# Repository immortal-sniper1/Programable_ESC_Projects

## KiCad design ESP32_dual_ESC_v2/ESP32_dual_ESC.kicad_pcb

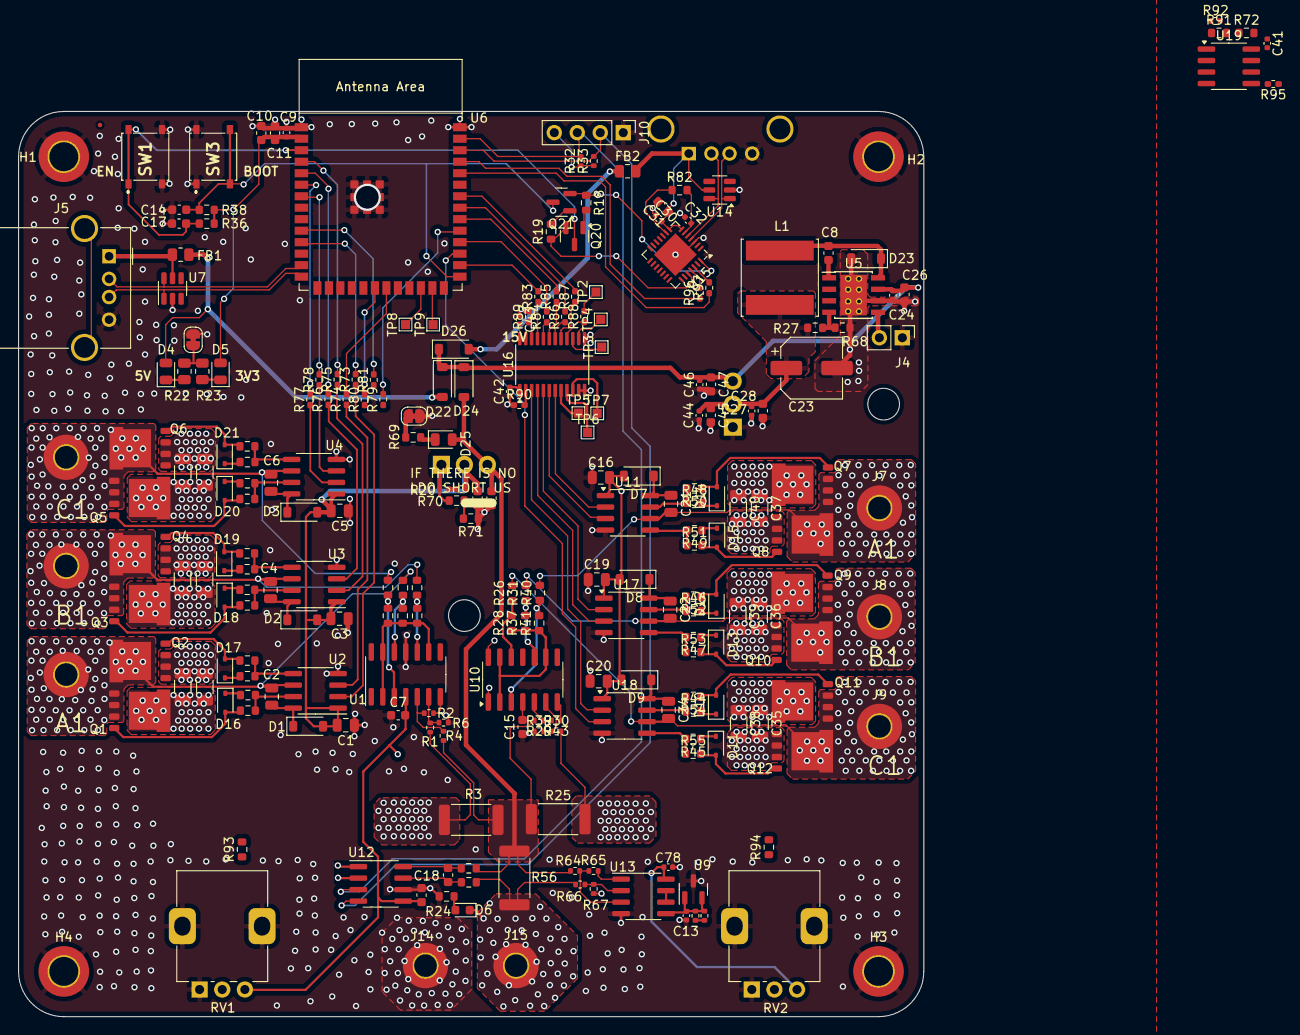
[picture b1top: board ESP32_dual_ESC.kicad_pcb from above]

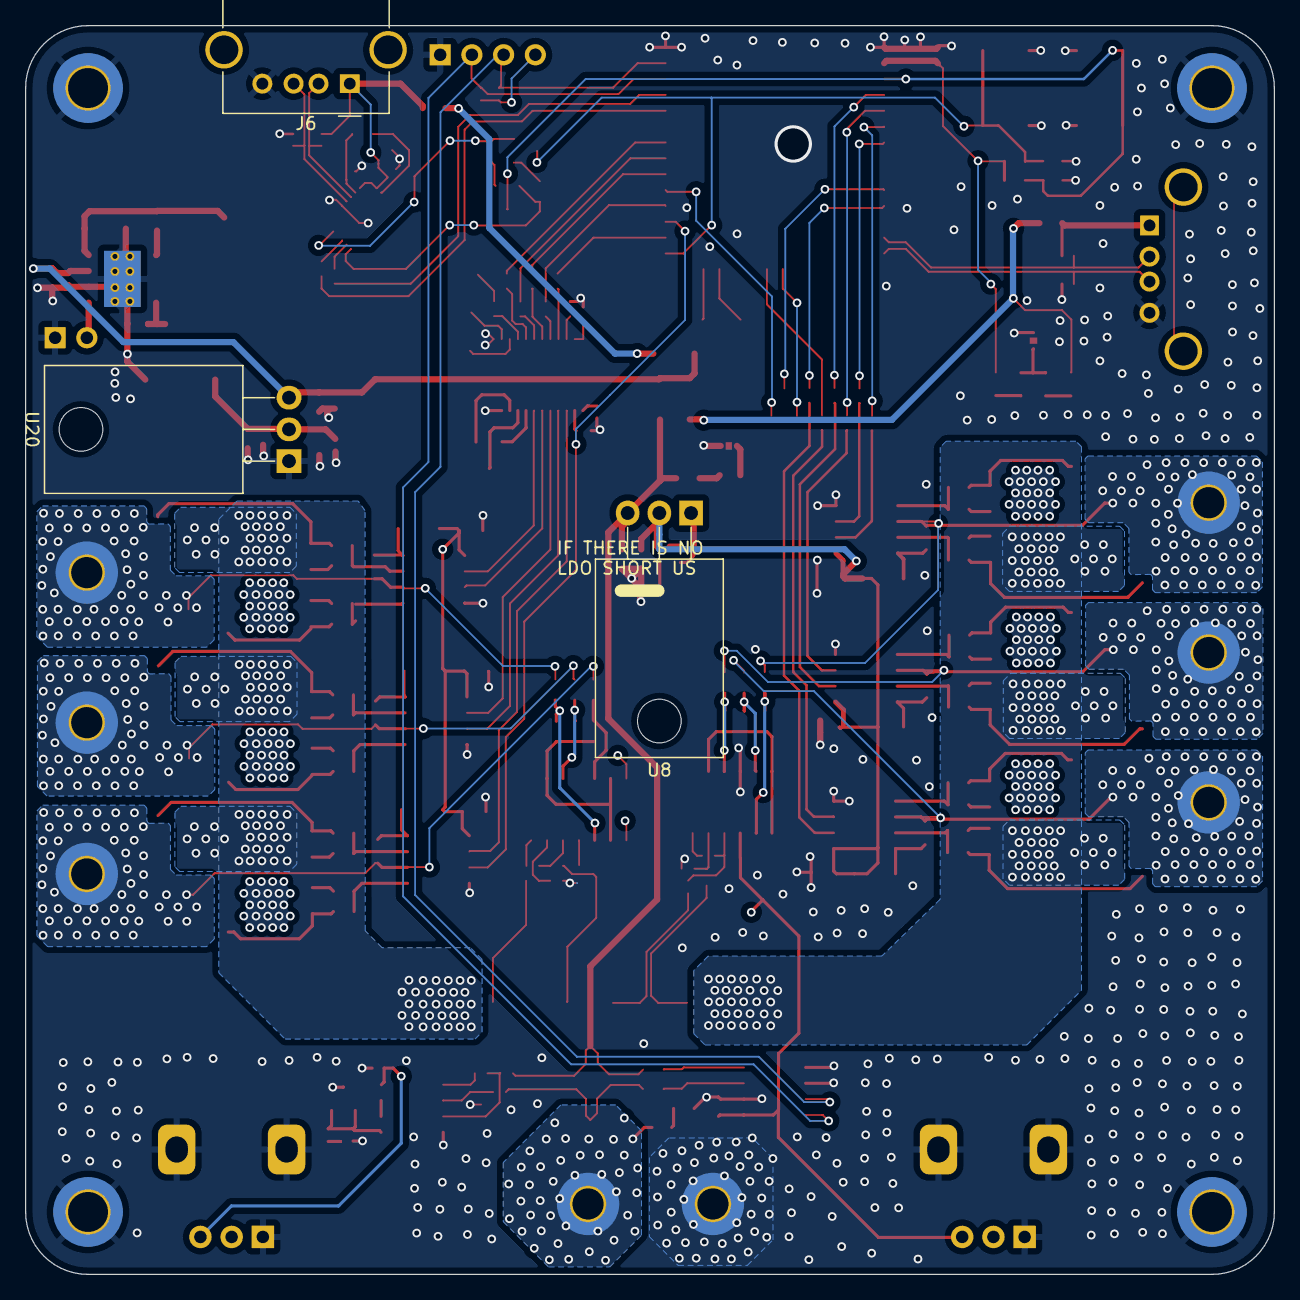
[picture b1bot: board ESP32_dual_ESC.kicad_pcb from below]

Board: 4 copper layers, 100.0 x 100.0 mm, 246 parts (3 on the bottom side), 170 nets.

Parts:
C1, C3, C5, C16, C19, C20: 10u@50V; C_0805_2012Metric
C2, C4, C6, C21, C22, C34: 10u; C_0805_2012Metric
C7, C8, C14, C15, C17, C25: 100n; C_0603_1608Metric
C9, C13, C24, C27, C30, C32, C41, C42, C43, C44, C46, C78: 1u; C_0402_1005Metric
C10, C11, C12, C18, C26, C28, C29, C31, C45, C47: 10u; C_0603_1608Metric
C23: 100u; CP_Elec_6.3x5.4
C35, C36, C37, C38, C39, C40, C72, C73, C74, C75, C76, C77: 10u; C_1206_3216Metric
D1, D2, D3, D7, D8, D9, D22, D23, D24, D26: B5819W_SL; D_SOD-123
D4, D5, D25: green; LED_0805_2012Metric
D6: red; LED_0603_1608Metric
D10, D11, D12, D13, D14, D15, D16, D17, D18, D19, D20, D21: 1N5819WS; D_SOD-323
FB1, FB2: FerriteBead_Small; R_0805_2012Metric
FID1: Fiducial; Fiducial_0.5mm_Mask1mm
FID2: Fiducial; KiCad-Logo2_5mm_SilkScreen
FID3: Fiducial; WEEE-Logo_4.2x6mm_SilkScreen
H1, H2, H3, H4: hole; MountingHole_3.2mm_M3_DIN965_Pad_TopBottom
J1, J9, J14, J15: A; MountingHole_2.5mm_Pad_TopBottom
J2, J8: B; MountingHole_2.5mm_Pad_TopBottom
J3, J7: C; MountingHole_2.5mm_Pad_TopBottom
J4: Conn_01x02; PinHeader_1x02_P2.54mm_Vertical
J5, J6: USB_A; USB_A_Molex_67643_Horizontal
J10: Conn_01x04; PinHeader_1x04_P2.54mm_Vertical
JP1, JP2: Jumper_2_Bridged; SolderJumper-2_P1.3mm_Bridged_RoundedPad1.0x1.5mm
L1: 75u; L_Changjiang_FNR8040S
Q1, Q2, Q3, Q4, Q5, Q6, Q7, Q8, Q9, Q10, Q11, Q12: HYG025N06LS1C2; DFN-8_(5x6)
Q20, Q21: MMBT5551L; SOT-23
R1, R4, R29, R30, R64, R66: 1k; R_0402_1005Metric
R2, R6, R39, R43, R65, R67: 75k; R_0402_1005Metric
R3, R25, R56: 1m; R_2512_6332Metric
R5, R7, R8, R12, R16, R17, R42, R44, R45, R46, R47, R48, R49, R50, R51, R52, R53, R54, R55, R59, R60, R61, R62, R63: 56; R_0603_1608Metric
R9, R10, R11, R26, R31, R40: 75k; R_0603_1608Metric
R13, R14, R15, R27, R28, R37, R41, R69: 10K; R_0603_1608Metric
R18, R19, R36, R38, R70, R71, R72, R82, R91, R93, R94: 10k; R_0603_1608Metric
R20, R34: 470; R_0402_1005Metric
R21, R35, R92: 2k; R_0402_1005Metric
R22, R23: 1k; R_0805_2012Metric
R24: 1k; R_0603_1608Metric
R32, R33: 5k1; R_0402_1005Metric
R57, R58: 5R1; R_0603_1608Metric
R68: 6.2k; R_0603_1608Metric
R73, R74, R75, R76, R77, R78, R79, R80, R81, R83, R84, R85, R86, R87, R88, R89, R90, R95, R96, R97: 0; R_0402_1005Metric_Pad0.72x0.64mm_HandSolder
RV1, RV2: R_Potentiometer_MountingPin; Potentiometer_Alps_RK09K_Single_Vertical
SW1, SW3: MCU_RESET; PTS526SK15SMTR2LFS
TP2, TP3, TP4, TP5, TP6, TP7, TP8, TP9: TestPoint; TestPoint_Pad_1.0x1.0mm
U1, U10: LM324; SOIC-14_3.9x8.7mm_P1.27mm
U2, U3, U4, U11, U17, U18: LM5109BMA; SOIC-8_3.9x4.9mm_P1.27mm
U5: TPS5430DDA; TI_SO-PowerPAD-8_ThermalVias
U6: ESP32-S3-WROOM-1
U7, U14: SRV05-4; SOT-23-6
U8: LM317_TO-220; TO-220-3_Horizontal_TabDown
U9: CJ431; SOT-23
U12: INA219AxD; SOIC-8_3.9x4.9mm_P1.27mm
U13, U19: MCP6002-xSN; SOIC-8_3.9x4.9mm_P1.27mm
U15: CP2102N-Axx-xQFN28; QFN-28-1EP_5x5mm_P0.5mm_EP3.35x3.35mm
U16: SN74AVC8T245PW; TSSOP-24_4.4x7.8mm_P0.65mm
U20: LM1117T-3.3; TO-220-3_Horizontal_TabDown

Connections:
1V8: C43.2, R93.2, R94.2, U16.23 (VCCB), U16.24 (VCCB), U19.1, U19.2 (-)
5v_2: D26.2 (A), FB2.1
+3V3: C7.2, C9.2, C10.1, C11.1, C15.2, C18.1, C23.1, C27.2, C28.1, C41.2, C42.2, C44.2, C45.1, C78.2, D5.2 (A), J10.4, L1.1, R27.2, R32.1, R33.1, R36.1, R38.2, R72.2, U1.4 (V+), U6.2 (3V3), U10.4 (V+), U12.5 (VS), U13.8 (V+), U16.1 (VCCA), U19.8 (V+), U20.2 (VO)
+5V: D4.2 (A), D22.2 (A), FB1.1
+15V: C1.2, C3.2, C5.2, C12.1, C16.2, C19.2, C20.2, D1.2 (A), D2.2 (A), D3.2 (A), D7.2 (A), D8.2 (A), D9.2 (A), R21.1, U2.1 (VDD), U3.1 (VDD), U4.1 (VDD), U8.2 (VO), U11.1 (VDD), U17.1 (VDD), U18.1 (VDD)
+VDC: R34.2, R35.1
/ESC_V1/A1: C2.2, J1.1, Q1.2 (S), Q2.1 (D), R9.2, U2.6 (HS)
/ESC_V1/B1: C4.2, J2.1, Q3.2 (S), Q4.1 (D), R10.2, U3.6 (HS)
/ESC_V1/BEMC_Phase_A: R79.1, U1.14
/ESC_V1/BEMC_Phase_B: R80.1, U1.8
/ESC_V1/BEMC_Phase_C: R81.1, U1.1
/ESC_V1/C1: C6.2, J3.1, Q5.2 (S), Q6.1 (D), R11.2, U4.6 (HS)
/ESC_V1/ESC_VCC: C72.1, C73.1, C74.1, C75.1, C76.1, C77.1, Q1.1 (D), Q3.1 (D), Q5.1 (D), R1.2, R3.2
/ESC_V1/HB1: C2.1, D1.1 (K), U2.8 (HB)
/ESC_V1/HB2: C4.1, D2.1 (K), U3.8 (HB)
/ESC_V1/HB3: C6.1, D3.1 (K), U4.8 (HB)
/ESC_V1/HO1: R17.2, R42.1, U2.7 (HO)
/ESC_V1/HO2: R7.1, R60.2, U3.7 (HO)
/ESC_V1/HO3: R12.1, R62.2, U4.7 (HO)
/ESC_V1/LO1: R5.1, R59.2, U2.5 (LO)
/ESC_V1/LO2: R8.1, R61.2, U3.5 (LO)
/ESC_V1/LO3: R16.1, R63.2, U4.5 (LO)
/ESC_V1/Phase_A_H: R73.1, U2.2 (HI)
/ESC_V1/Phase_A_L: R74.1, U2.3 (LI)
/ESC_V1/Phase_B_H: R75.1, U3.2 (HI)
/ESC_V1/Phase_B_L: R76.1, U3.3 (LI)
/ESC_V1/Phase_C_H: R77.1, U4.2 (HI)
/ESC_V1/Phase_C_L: R78.1, U4.3 (LI)
/ESC_V1/gate_H1: D16.2 (A), Q1.3 (G), R17.1
/ESC_V1/gate_H2: D18.2 (A), Q3.3 (G), R60.1
/ESC_V1/gate_H3: D20.2 (A), Q5.3 (G), R62.1
/ESC_V1/gate_L1: D17.2 (A), Q2.3 (G), R5.2
/ESC_V1/gate_L2: D19.2 (A), Q4.3 (G), R8.2
/ESC_V1/gate_L3: D21.2 (A), Q6.3 (G), R16.2
/ESC_V1/star2: R13.1, R14.1, R15.1, U1.2 (-), U1.9 (-), U1.13 (-)
/ESC_V2/A1: C34.2, J9.1, Q11.2 (S), Q12.1 (D), R26.2, U18.6 (HS)
/ESC_V2/B1: C22.2, J8.1, Q9.2 (S), Q10.1 (D), R31.2, U17.6 (HS)
/ESC_V2/C1: C21.2, J7.1, Q7.2 (S), Q8.1 (D), R40.2, U11.6 (HS)
/ESC_V2/ESC_VCC: C35.1, C36.1, C37.1, C38.1, C39.1, C40.1, Q7.1 (D), Q9.1 (D), Q11.1 (D), R25.2, R30.2
/ESC_V2/HB1: C34.1, D9.1 (K), U18.8 (HB)
/ESC_V2/HB2: C22.1, D8.1 (K), U17.8 (HB)
/ESC_V2/HB3: C21.1, D7.1 (K), U11.8 (HB)
/ESC_V2/HO1: R44.1, R54.2, U18.7 (HO)
/ESC_V2/HO2: R46.1, R52.2, U17.7 (HO)
/ESC_V2/HO3: R48.1, R50.2, U11.7 (HO)
/ESC_V2/LO1: R45.2, R55.1, U18.5 (LO)
/ESC_V2/LO2: R47.2, R53.1, U17.5 (LO)
/ESC_V2/LO3: R49.2, R51.1, U11.5 (LO)
/ESC_V2/Phase_A_H: U16.3 (A1), U18.2 (HI)
/ESC_V2/Phase_B_H: U16.5 (A3), U17.2 (HI)
/ESC_V2/Phase_B_L: U16.4 (A2), U17.3 (LI)
/ESC_V2/Phase_C_H: U11.2 (HI), U16.7 (A5)
/ESC_V2/Phase_C_L: U11.3 (LI), U16.6 (A4)
/ESC_V2/gate_H1: D10.2 (A), Q11.3 (G), R54.1
/ESC_V2/gate_H2: D12.2 (A), Q9.3 (G), R52.1
/ESC_V2/gate_H3: D14.2 (A), Q7.3 (G), R50.1
/ESC_V2/gate_L1: D11.2 (A), Q12.3 (G), R55.2
/ESC_V2/gate_L2: D13.2 (A), Q10.3 (G), R53.2
/ESC_V2/gate_L3: D15.2 (A), Q8.3 (G), R51.2
/ESC_V2/star2: R28.1, R37.1, R41.1, U10.2 (-), U10.9 (-), U10.13 (-)
/MCU/2V5_RAW: C13.2, R34.1, R35.2, U9.1 (REF), U9.2 (K), U13.5 (+)
/MCU/DTR: Q21.2 (E), R18.1, U15.28 (~DTR)
/MCU/ESP_BOOT: C17.1, Q21.3 (C), R38.1, SW3.2 (B), U6.27 (GPIO0/BOOT)
/MCU/ESP_EN: C14.2, Q20.3 (C), R36.2, SW1.1 (A), U6.3 (EN)
/MCU/GPIO_04: R75.2, U6.4 (GPIO4/TOUCH4/ADC1_CH3)
/MCU/GPIO_05: R76.2, U6.5 (GPIO5/TOUCH5/ADC1_CH4)
/MCU/GPIO_06: R77.2, U6.6 (GPIO6/TOUCH6/ADC1_CH5)
/MCU/GPIO_07: R78.2, U6.7 (GPIO7/TOUCH7/ADC1_CH6)
/MCU/GPIO_08: R2.1, U1.7, U6.12 (GPIO8/TOUCH8/ADC1_CH7/SUBSPICS1)
/MCU/GPIO_11: R43.1, U6.19 (GPIO11/TOUCH11/ADC2_CH0/FSPID/FSPIIO5/S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), U10.7
/MCU/GPIO_12: R80.2, U6.20 (GPIO12/TOUCH12/ADC2_CH1/FSPICLK/FSPIIO6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)
/MCU/GPIO_13: R74.2, U6.21 (GPIO13/TOUCH13/ADC2_CH2/FSPIQ/FSPIIO7/S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)
/MCU/GPIO_14: U6.22 (GPIO14/TOUCH14/ADC2_CH3/FSPIWP/FSPIDQS/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), U10.8
/MCU/GPIO_15: RV2.2, U6.8 (GPIO15/U0RTS/ADC2_CH4/XTAL_32K_P)
/MCU/GPIO_16: RV1.2, U6.9 (GPIO16/U0CTS/ADC2_CH5/XTAL_32K_N)
/MCU/GPIO_17: R81.2, U6.10 (GPIO17/U1TXD/ADC2_CH6)
/MCU/GPIO_18: R73.2, U6.11 (GPIO18/U1RXD/ADC2_CH7/CLK_OUT3)
/MCU/GPIO_21: U6.23 (GPIO21), U10.1
/MCU/GPIO_35: R83.2, U6.28 (SPIIO6/GPIO35/FSPID/SUBSPID)
/MCU/GPIO_36: U6.29 (SPIIO7/GPIO36/FSPICLK/SUBSPICLK), U18.3 (LI)
/MCU/GPIO_37: R84.2, U6.30 (SPIDQS/GPIO37/FSPIQ/SUBSPIQ)
/MCU/GPIO_38: R79.2, U6.31 (GPIO38/FSPIWP/SUBSPIWP)
/MCU/GPIO_39: R85.2, U6.32 (MTCK/GPIO39/CLK_OUT3/SUBSPICS1)
/MCU/GPIO_40: R86.2, U6.33 (MTDO/GPIO40/CLK_OUT2)
/MCU/GPIO_41: R87.2, U6.34 (MTDI/GPIO41/CLK_OUT1)
/MCU/GPIO_42: U6.35 (MTMS/GPIO42), U10.14
/MCU/GPIO_47: TP8.1, U6.24 (GPIO47/SPICLK_P/SUBSPICLK_P_DIFF)
/MCU/GPIO_48: TP9.1, U6.25 (GPIO48/SPICLK_N/SUBSPICLK_N_DIFF)
/MCU/RST: Q20.2 (E), R19.1, U15.24 (~RTS)
/MCU/RX: R96.2, U15.25 (RXD)
/MCU/RX_in: R96.1, U6.37 (U0TXD/GPIO43/CLK_OUT1)
/MCU/TX: R97.2, U15.26 (TXD)
/MCU/TX_in: R97.1, U6.36 (U0RXD/GPIO44/CLK_OUT2)
/MCU/Vusb_2: C30.2, C31.1, FB2.2, J6.1 (VBUS), U14.5 (VP), U15.7 (VREGIN), U15.8 (VBUS)
D2+: J6.3 (D+), U14.1 (IO1), U15.4 (D+)
D2-: J6.2 (D-), U14.6 (IO4), U15.5 (D-)
D+: J5.3 (D+), U6.14 (GPIO20/U1CTS/ADC2_CH9/CLK_OUT1/USB_D+), U7.1 (IO1)
D-: J5.2 (D-), U6.13 (GPIO19/U1RTS/ADC2_CH8/CLK_OUT2/USB_D-), U7.6 (IO4)
GND: C1.1, C3.1, C5.1, C7.1, C9.1, C10.2, C11.2, C12.2, C13.1, C14.1, C15.1, C16.1, C17.2, C18.2, C19.1, C20.1, C23.2, C24.1, C26.2, C27.1, C28.2, C29.2, C30.1, C31.2, C32.1, C35.2, C36.2, C37.2, C38.2, C39.2, C40.2, C41.1, C42.1, C43.1, C44.1, C45.2, C46.1, C47.2, C72.2, C73.2, C74.2, C75.2, C76.2, C77.2, C78.1, D23.2 (A), H1.1, H2.1, H3.1, H4.1, J4.1, J5.4 (GND), J6.4 (GND), J10.1, J14.1, JP1.1 (A), JP2.1 (A), Q2.2 (S), Q4.2 (S), Q6.2 (S), Q8.2 (S), Q10.2 (S), Q12.2 (S), R6.1, R24.1, R39.1, R67.1, R68.2, R71.1, R89.2, R90.1, R92.2, R95.1, RV1.1, RV1.MP (MountPin), RV2.1, RV2.MP (MountPin), SW1.2 (B), SW3.1 (A), U1.11 (V-), U2.4 (VSS), U3.4 (VSS), U4.4 (VSS), U5.6 (GND), U5.9 (GNDPAD), U6.1 (GND), U6.40 (GND), U6.41 (GND), U7.2 (VN), U9.3 (A), U10.11 (V-), U11.4 (VSS), U12.1 (A1), U12.2 (A0), U12.6 (GND), U13.4 (V-), U14.2 (VN), U15.3 (GND), U15.29 (GND), U16.11 (GND), U16.12 (GND), U16.13 (GND), U17.4 (VSS), U18.4 (VSS), U19.4 (V-), U20.1 (GND)
unnamed: D4.1 (K), R22.1
unnamed: D5.1 (K), R23.1
unnamed: D6.2 (A), R24.2
unnamed: D10.1 (K), R44.2
unnamed: D11.1 (K), R45.1
unnamed: D12.1 (K), R46.2
unnamed: D13.1 (K), R47.1
unnamed: D14.1 (K), R48.2
unnamed: D15.1 (K), R49.1
unnamed: D16.1 (K), R42.2
unnamed: D17.1 (K), R59.1
unnamed: D18.1 (K), R7.2
unnamed: D19.1 (K), R61.1
unnamed: D20.1 (K), R12.2
unnamed: D21.1 (K), R63.1
unnamed: C24.2, C26.1, C46.2, C47.1, D22.1 (K), D24.1 (K), D26.1 (K), U5.7 (VIN), U20.3 (VI)
unnamed: C8.1, D23.1 (K), L1.2, U5.8 (PH)
unnamed: D25.1 (K), R69.2
unnamed: J4.2, U5.5 (EN)
unnamed: JP1.2 (B), R22.2, R23.2
unnamed: JP2.2 (B), R69.1
unnamed: Q20.1 (B), R18.2
unnamed: Q21.1 (B), R19.2
unnamed: R20.2, R21.2
unnamed: R70.1, R71.2
unnamed: R88.2, TP2.1
unnamed: R91.1, R92.1
unnamed: R93.1, RV1.3
unnamed: R94.1, RV2.3
unnamed: R11.1, R15.2, U1.3 (+)
unnamed: R2.2, R4.1, U1.5 (+)
unnamed: R1.1, R6.2, U1.6 (-)
unnamed: R10.1, R14.2, U1.10 (+)
unnamed: R9.1, R13.2, U1.12 (+)
unnamed: C8.2, U5.1 (BOOT)
unnamed: R27.1, R68.1, U5.4 (VSENSE)
unnamed: R20.1, R70.2, U8.1 (ADJ)
unnamed: R40.1, R41.2, U10.3 (+)
unnamed: R29.1, R43.2, U10.5 (+)
unnamed: R30.1, R39.2, U10.6 (-)
unnamed: R31.1, R37.2, U10.10 (+)
unnamed: R26.1, R28.2, U10.12 (+)
unnamed: C25.1, R57.2, U12.8 (IN+)
unnamed: C25.2, R58.2, U12.7 (IN-)
unnamed: R64.2, R65.1, U13.3 (+)
unnamed: R66.2, R67.2, U13.2 (-)
unnamed: C32.2, R82.2, U15.6 (VDD)
unnamed: R82.1, U15.9 (~RST)
unnamed: TP5.1, U16.8 (A6)
unnamed: TP6.1, U16.9 (A7)
unnamed: TP7.1, U16.10 (A8)
unnamed: R83.1, U16.21 (B1)
unnamed: R84.1, U16.20 (B2)
unnamed: R85.1, U16.19 (B3)
unnamed: R86.1, U16.18 (B4)
unnamed: R87.1, U16.17 (B5)
unnamed: R88.1, U16.16 (B6)
unnamed: TP3.1, U16.15 (B7)
unnamed: TP4.1, U16.14 (B8)
unnamed: R90.2, U16.2 (DIR)
unnamed: R89.1, U16.22 (~OE)
unnamed: R72.1, R91.2, U19.3 (+)
unnamed: R95.2, U19.5 (+)
unnamed: U19.6 (-), U19.7
REF_2v5: U6.18 (GPIO10/TOUCH10/ADC1_CH9/FSPICS0/FSPIIO4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), U13.6 (-), U13.7
SCL: J10.2, R33.2, U6.38 (GPIO2/TOUCH2/ADC1_CH1), U12.4 (SCL)
SDA: J10.3, R32.2, U6.39 (GPIO1/TOUCH1/ADC1_CH0), U12.3 (SDA)
VBUS: FB1.2, J5.1 (VBUS), U7.5 (VP)
VCC: C29.1, D24.2 (A), D25.2 (A), R3.1, R4.2, R25.1, R29.2, R56.1, R57.1, R64.1, U8.3 (VI)
VDC: D6.1 (K), J15.1, R56.2, R58.1, R66.1
current: R65.2, U6.17 (GPIO9/TOUCH9/ADC1_CH8/FSPIHD/SUBSPIHD), U13.1

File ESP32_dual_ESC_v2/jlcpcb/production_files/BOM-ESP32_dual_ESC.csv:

Comment,Designator,Footprint,LCSC
FerriteBead_Small,"FB1,FB2",R_0805_2012Metric,C1015
LM5109BMA,"U11,U17,U18,U2,U3,U4",SOIC-8_3.9x4.9mm_P1.27mm,C116862
1k,"R1,R29,R30,R4,R64,R66",R_0402_1005Metric,C11702
10u,"C35,C36,C37,C38,C39,C40,C72,C73,C74,C75,C76,C77",C_1206_3216Metric,C13585
100n,"C14,C15,C17,C25,C7,C8",C_0603_1608Metric,C14663
10u,"C2,C21,C22,C34,C4,C6",C_0805_2012Metric,C15850
0,"R73,R74,R75,R76,R77,R78,R79,R80,R81,R83,R84,R85,R86,R87,R88,R89,R90,R96,R97",R_0402_1005Metric_Pad0.72x0.64mm_HandSolder,C17168
1k,"R22,R23",R_0805_2012Metric,C17513
1N5819WS,"D10,D11,D12,D13,D14,D15,D16,D17,D18,D19,D20,D21",D_SOD-323,C191023
1k,R24,R_0603_1608Metric,C21190
MMBT5551L,"Q20,Q21",SOT-23,C2145
red,D6,LED_0603_1608Metric,C2286
green,"D25,D4,D5",LED_0805_2012Metric,C2297
75k,"R10,R11,R26,R31,R40,R9",R_0603_1608Metric,C23242
470,"R20,R34",R_0402_1005Metric,C25117
56,"R12,R16,R17,R42,R44,R45,R46,R47,R48,R49,R5,R50,R51,R52,R53,R54,R55,R59,R60,R61,R62,R63,R7,R8",R_0603_1608Metric,C25196
5R1,"R57,R58",R_0603_1608Metric,C25197
75k,"R2,R39,R43,R6,R65,R67",R_0402_1005Metric,C25798
10k,"R100,R101,R13,R14,R15,R18,R19,R27,R28,R36,R37,R38,R41,R69,R70,R71,R72,R82,R91,R93,R94,R95,R98,R99",R_0603_1608Metric,C25804
5k1,"R32,R33",R_0402_1005Metric,C25905
HYG025N06LS1C2,"Q1,Q10,Q11,Q12,Q2,Q3,Q4,Q5,Q6,Q7,Q8,Q9",DFN-8_(5x6),C2827231
CJ431,U9,SOT-23,C3113
MCU_RESET,"SW1,SW3",PTS526SK15SMTR2LFS,C318884
2k,"R102,R21,R35,R92",R_0402_1005Metric,C4109
6.2k,R68,R_0603_1608Metric,C4260
10u@50V,"C1,C16,C19,C20,C3,C5",C_0805_2012Metric,C440198
100u,C23,CP_Elec_6.3x5.4,C4747963
1u,"C13,C24,C27,C30,C32,C33,C41,C42,C43,C44,C46,C78,C9",C_0402_1005Metric,C52923
SN74AVC8T245PW,U16,TSSOP-24_4.4x7.8mm_P0.65mm,C546420
CP2102N-Axx-xQFN28,U15,QFN-28-1EP_5x5mm_P0.5mm_EP3.35x3.35mm,C6568
LM324,"U1,U10",SOIC-14_3.9x8.7mm_P1.27mm,C71035
MCP6002-xSN,"U13,U19",SOIC-8_3.9x4.9mm_P1.27mm,C7377
SRV05-4,"U14,U7",SOT-23-6,C85364
B5819W_SL,"D1,D2,D22,D23,D24,D26,D3,D7,D8,D9",D_SOD-123,C8598
10u,"C10,C11,C12,C18,C26,C28,C29,C31,C45,C47",C_0603_1608Metric,C96446
TPS5430DDA,U5,TI_SO-PowerPAD-8_ThermalVias,C9864
TestPoint,TP5,TestPoint_Pad_1.0x1.0mm,
Conn_01x02,J4,PinHeader_1x02_P2.54mm_Vertical,
1m,R25,R_2512_6332Metric,
R_Potentiometer_MountingPin,RV2,Potentiometer_Alps_RK09K_Single_Vertical,
1m,R3,R_2512_6332Metric,
USB_A,J5,USB_A_Molex_67643_Horizontal,
TestPoint,TP8,TestPoint_Pad_1.0x1.0mm,
R_Potentiometer_MountingPin,RV1,Potentiometer_Alps_RK09K_Single_Vertical,
TestPoint,TP6,TestPoint_Pad_1.0x1.0mm,
TestPoint,TP3,TestPoint_Pad_1.0x1.0mm,
INA219AxD,U12,SOIC-8_3.9x4.9mm_P1.27mm,
TestPoint,TP4,TestPoint_Pad_1.0x1.0mm,
TestPoint,TP9,TestPoint_Pad_1.0x1.0mm,
75u,L1,L_Changjiang_FNR8040S,
1m,R56,R_2512_6332Metric,
TestPoint,TP7,TestPoint_Pad_1.0x1.0mm,
TestPoint,TP2,TestPoint_Pad_1.0x1.0mm,
ESP32-S3-WROOM-1,U6,ESP32-S3-WROOM-1,
LM1117T-3.3,U20,TO-220-3_Horizontal_TabDown,
LM317_TO-220,U8,TO-220-3_Horizontal_TabDown,
USB_A,J6,USB_A_Molex_67643_Horizontal,

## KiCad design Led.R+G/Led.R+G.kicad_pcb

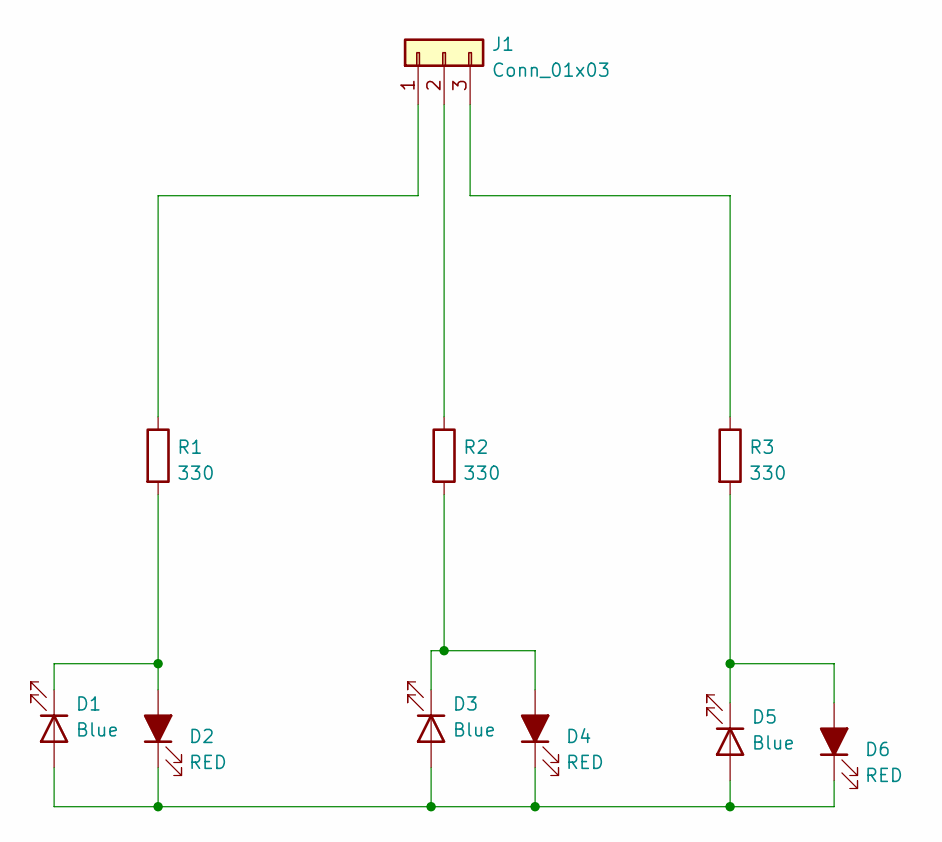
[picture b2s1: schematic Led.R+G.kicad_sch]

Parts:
D1, D3, D5: Blue; LED_D5.0mm
D2, D4, D6: RED; LED_D5.0mm
J1: Conn_01x03; TerminalBlock_Altech_AK300-3_P5.00mm
R1, R2, R3: 330; R_Axial_DIN0414_L11.9mm_D4.5mm_P15.24mm_Horizontal

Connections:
unnamed: D1.2 (A), D2.1 (K), D3.2 (A), D4.1 (K), D5.2 (A), D6.1 (K)
unnamed: J1.1, R1.1
unnamed: D1.1 (K), D2.2 (A), R1.2
unnamed: J1.2, R2.1
unnamed: D3.1 (K), D4.2 (A), R2.2
unnamed: J1.3, R3.1
unnamed: D5.1 (K), D6.2 (A), R3.2

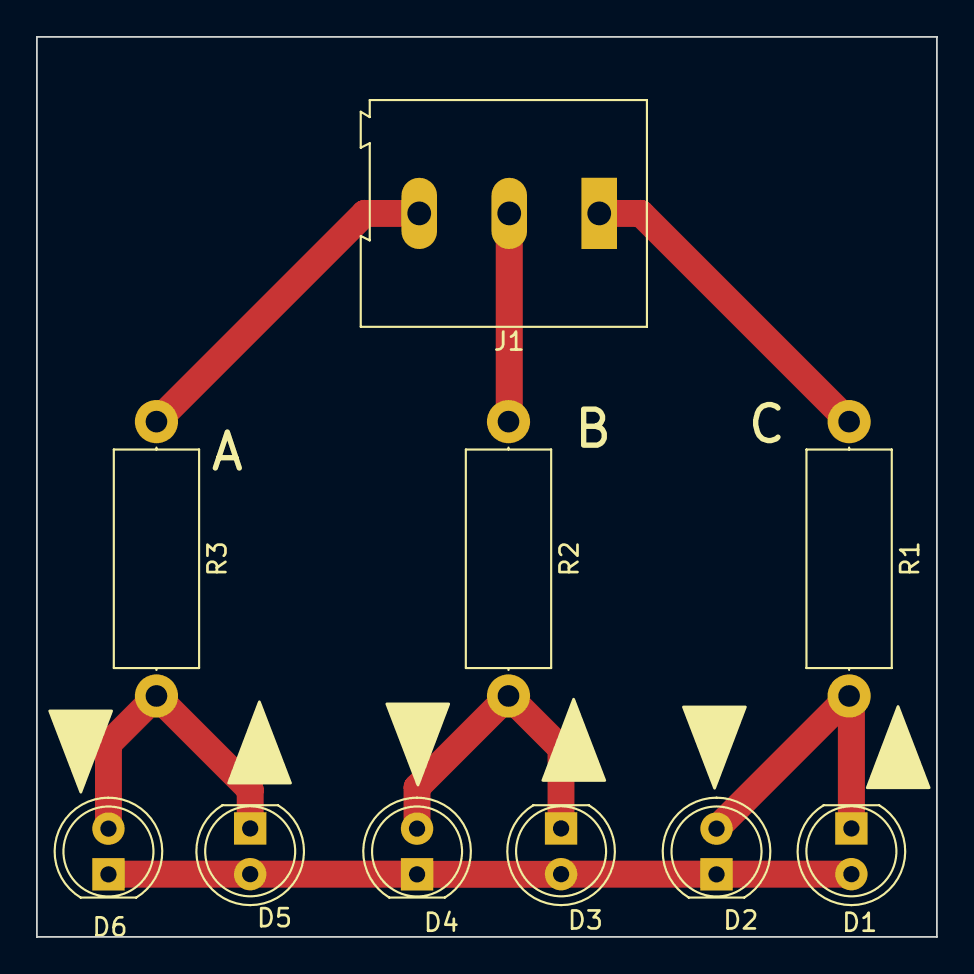
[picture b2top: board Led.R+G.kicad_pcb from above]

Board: 2 copper layers, 50.0 x 50.0 mm, 10 parts (0 on the bottom side), 7 nets.

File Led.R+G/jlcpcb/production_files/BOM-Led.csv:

Comment,Designator,Footprint,LCSC
330,R3,R_Axial_DIN0414_L11.9mm_D4.5mm_P15.24mm_Horizontal,
RED,D4,LED_D5.0mm,
RED,D2,LED_D5.0mm,
330,R1,R_Axial_DIN0414_L11.9mm_D4.5mm_P15.24mm_Horizontal,
Conn_01x03,J1,TerminalBlock_Altech_AK300-3_P5.00mm,
Blue,D5,LED_D5.0mm,
RED,D6,LED_D5.0mm,
Blue,D3,LED_D5.0mm,
330,R2,R_Axial_DIN0414_L11.9mm_D4.5mm_P15.24mm_Horizontal,
Blue,D1,LED_D5.0mm,

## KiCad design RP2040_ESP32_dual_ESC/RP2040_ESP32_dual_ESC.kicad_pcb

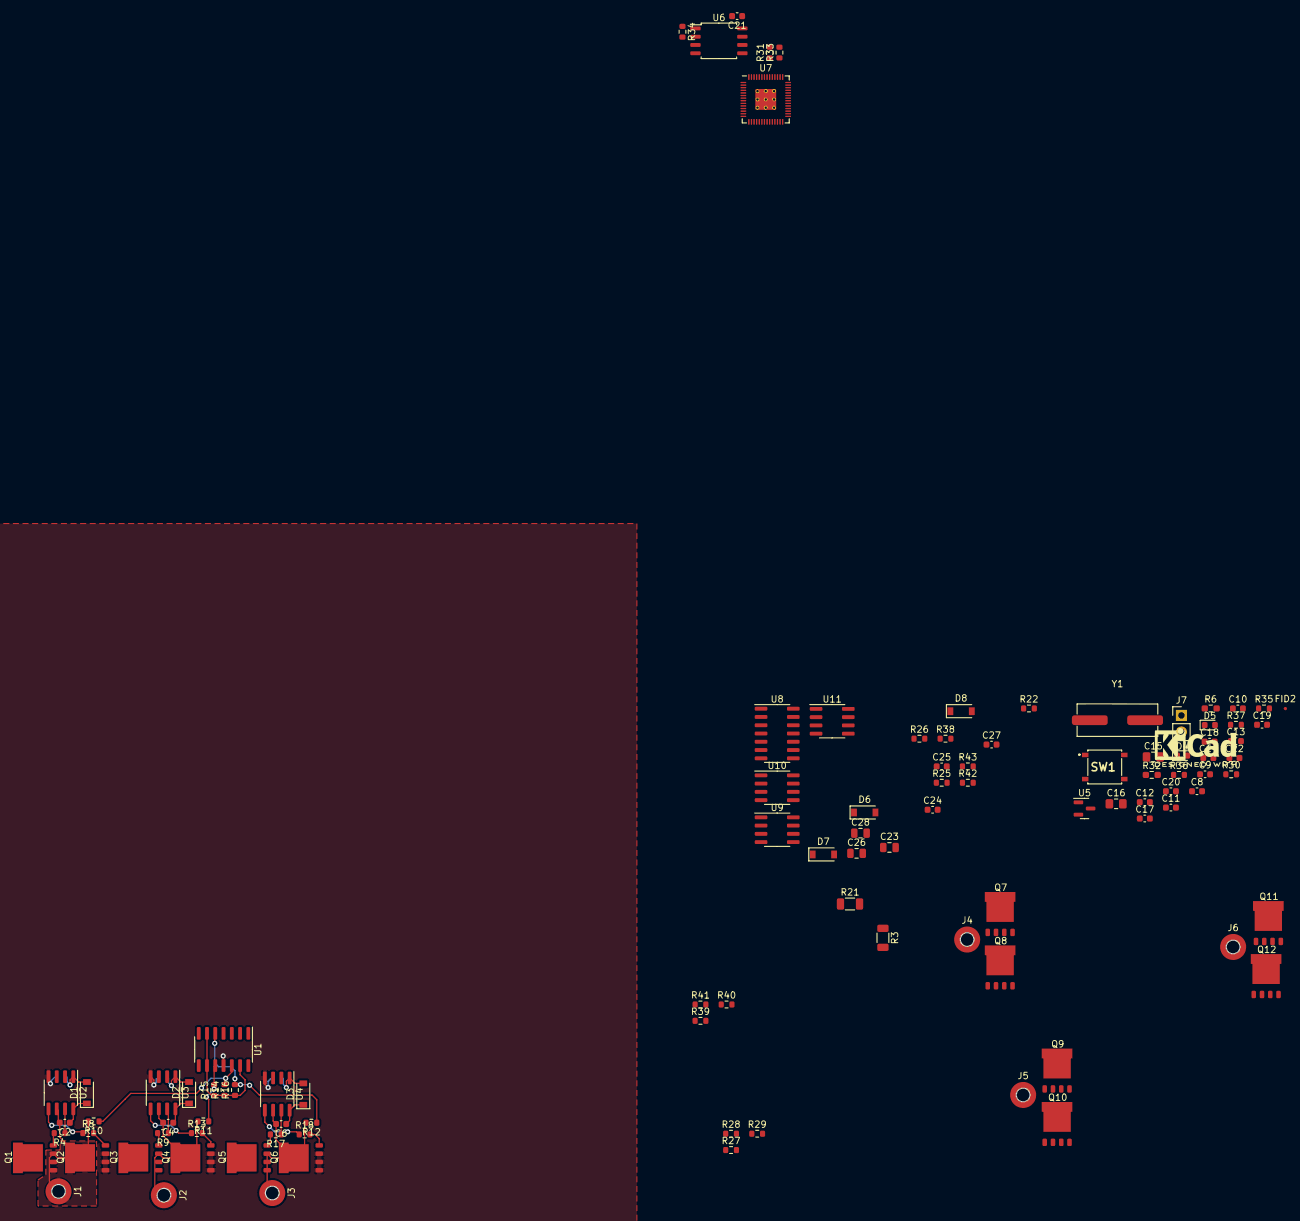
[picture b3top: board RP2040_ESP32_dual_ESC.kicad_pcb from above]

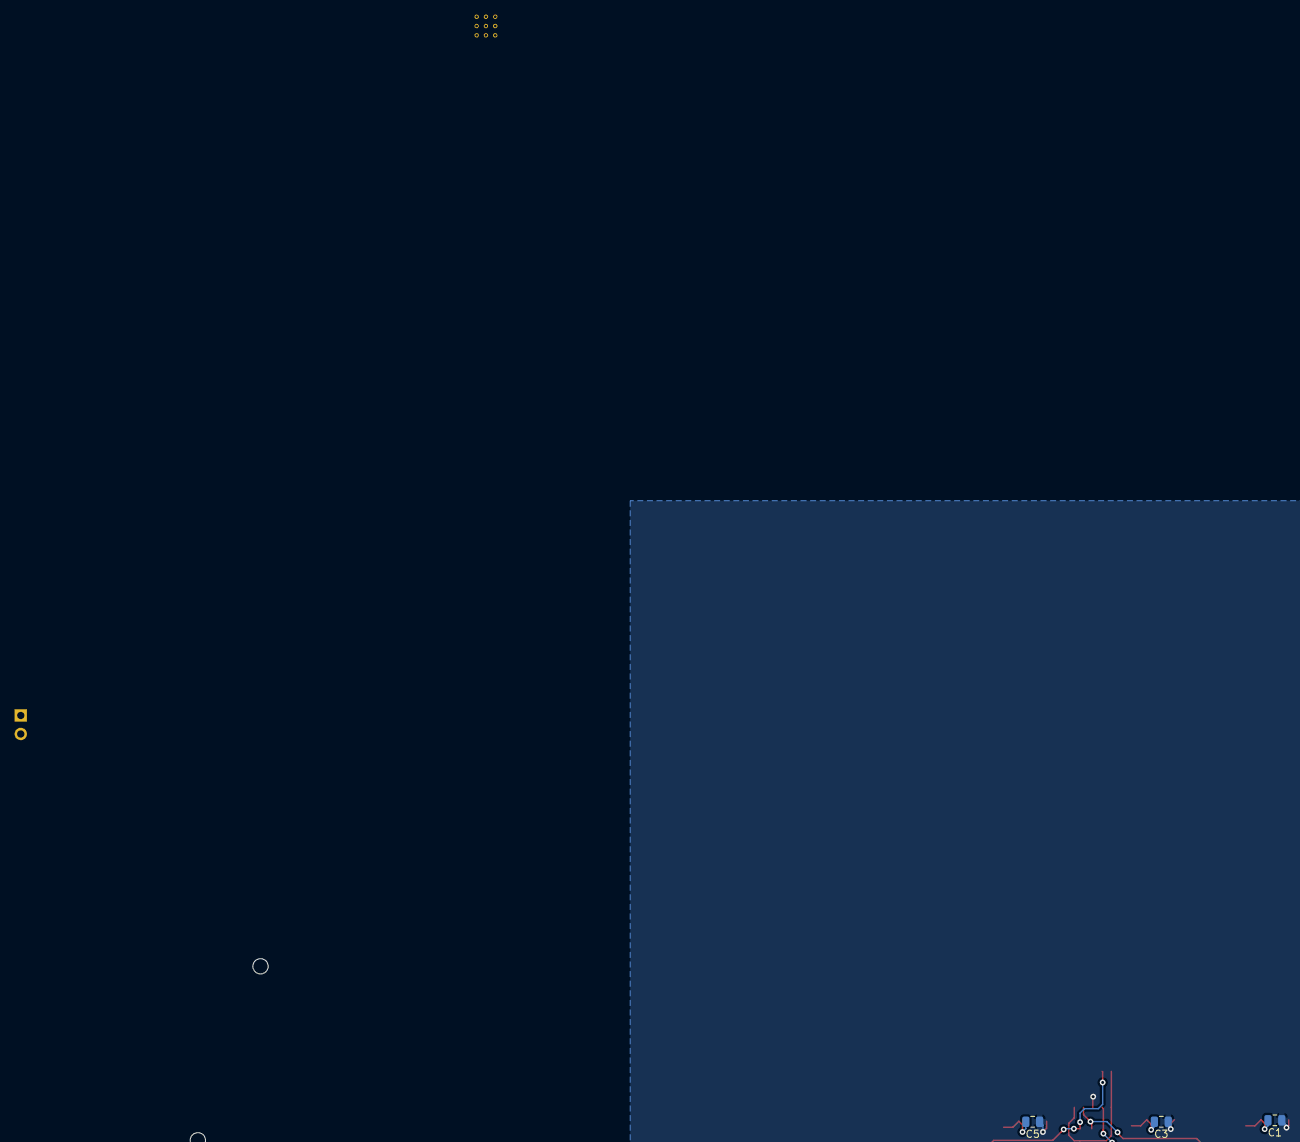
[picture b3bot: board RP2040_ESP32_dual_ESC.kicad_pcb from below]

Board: 2 copper layers, 105 parts (3 on the bottom side), 86 nets.

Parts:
C1, C3, C5, C23, C26, C28: 10u@50V; C_0805_2012Metric
C2, C4, C6, C18, C20, C24, C25, C27: 10u; C_0603_1608Metric
C8, C9, C10, C11, C12, C13, C14, C17, C19, C21, C22: 100n; C_0603_1608Metric
C15, C16: DNP; C_0805_2012Metric_Pad1.18x1.45mm_HandSolder
D1, D2, D3, D6, D7, D8: B5819W_SL; D_SOD-123
D4, D5: led; LED_0603_1608Metric
FID2: Fiducial; Fiducial_0.5mm_Mask1mm
FID3: Fiducial; KiCad-Logo2_5mm_SilkScreen
FID4: Fiducial; OSHW-Logo2_7.3x6mm_SilkScreen
J1, J4: A; Mounting_Wuerth_WA-SMSI-M1.6_H1.5mm_9774015633
J2, J5: B; Mounting_Wuerth_WA-SMSI-M1.6_H1.5mm_9774015633
J3, J6: C; Mounting_Wuerth_WA-SMSI-M1.6_H1.5mm_9774015633
J7: pins; PinHeader_1x02_P2.54mm_Vertical
Q1, Q2, Q3, Q4, Q5, Q6, Q7, Q8, Q9, Q10, Q11, Q12: HYG025N06LS1C2; DFN-8_(5x6)
R3, R21: 5m; R_1206_3216Metric
R4, R8, R9, R13, R17, R18, R22, R25, R26, R38, R42, R43: 22; R_0603_1608Metric
R6: 1k; R_0603_1608Metric_Pad0.98x0.95mm_HandSolder
R10, R11, R12, R27, R28, R29: 0; R_0603_1608Metric
R14, R15, R16, R39, R40, R41: 10K; R_0603_1608Metric
R30, R34: 1k; R_0603_1608Metric
R31, R33: 27; R_0603_1608Metric
R32: DNF; R_0603_1608Metric_Pad0.98x0.95mm_HandSolder
R35: 10k; R_0603_1608Metric
R36, R37: 330; R_0603_1608Metric
SW1: SW_SPST; PTS526SK15SMTR2LFS
U1, U8: LM324; SOIC-14_3.9x8.7mm_P1.27mm
U2, U3, U4, U9, U10, U11: LM5109BMA; SOIC-8_3.9x4.9mm_P1.27mm
U5: LM4040DBZ-3.0; SOT-23
U6: W25Q128JVS; SOIC-8_5.23x5.23mm_P1.27mm
U7: RP2040; RP2040-QFN-56
Y1: ABLS-12.000MHZ-B4-T; ATS120SM

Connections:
+1V1: C8.1, C9.1, C20.1, U7.23 (DVDD), U7.45 (VREG_VOUT), U7.50 (DVDD)
+3V3: C10.1, C11.1, C12.1, C13.1, C14.1, C17.1, C18.1, C21.1, R30.1, R32.1, R35.2, R37.2, U1.4 (V+), U6.8 (VCC), U7.1 (IOVDD), U7.10 (IOVDD), U7.22 (IOVDD), U7.33 (IOVDD), U7.42 (IOVDD), U7.44 (VREG_IN), U7.48 (USB_VDD), U7.49 (IOVDD), U8.4 (V+)
+15V: C1.2, C3.2, C5.2, C23.2, C26.2, C28.2, D1.2 (A), D2.2 (A), D3.2 (A), D6.2 (A), D7.2 (A), D8.2 (A), U2.1 (VDD), U3.1 (VDD), U4.1 (VDD), U9.1 (VDD), U10.1 (VDD), U11.1 (VDD)
/ESC1/A1: C24.2, J4.1, Q7.2 (S), Q8.1 (D), R27.2, U9.6 (HS)
/ESC1/B1: C25.2, J5.1, Q9.2 (S), Q10.1 (D), R28.2, U10.6 (HS)
/ESC1/C1: C27.2, J6.1, Q11.2 (S), Q12.1 (D), R29.2, U11.6 (HS)
/ESC1/HB1: C24.1, D6.1 (K), U9.8 (HB)
/ESC1/HB2: C25.1, D7.1 (K), U10.8 (HB)
/ESC1/HB3: C27.1, D8.1 (K), U11.8 (HB)
/ESC1/HO1: R22.1, U9.7 (HO)
/ESC1/HO2: R26.1, U10.7 (HO)
/ESC1/HO3: R42.1, U11.7 (HO)
/ESC1/LO1: R25.1, U9.5 (LO)
/ESC1/LO2: R38.1, U10.5 (LO)
/ESC1/LO3: R43.1, U11.5 (LO)
/ESC1/gate_H1: Q7.3 (G), R22.2
/ESC1/gate_H2: Q9.3 (G), R26.2
/ESC1/gate_H3: Q11.3 (G), R42.2
/ESC1/gate_L1: Q8.3 (G), R25.2
/ESC1/gate_L2: Q10.3 (G), R38.2
/ESC1/gate_L3: Q12.3 (G), R43.2
/ESC1/star2: R39.1, R40.1, R41.1, U8.6 (-), U8.9 (-), U8.13 (-)
/ESC2/A1: C2.2, J1.1, Q1.2 (S), Q2.1 (D), R10.2, U2.6 (HS)
/ESC2/B1: C4.2, J2.1, Q3.2 (S), Q4.1 (D), R11.2, U3.6 (HS)
/ESC2/C1: C6.2, J3.1, Q5.2 (S), Q6.1 (D), R12.2, U4.6 (HS)
/ESC2/HB1: C2.1, D1.1 (K), U2.8 (HB)
/ESC2/HB2: C4.1, D2.1 (K), U3.8 (HB)
/ESC2/HB3: C6.1, D3.1 (K), U4.8 (HB)
/ESC2/HO1: R4.1, U2.7 (HO)
/ESC2/HO2: R9.1, U3.7 (HO)
/ESC2/HO3: R17.1, U4.7 (HO)
/ESC2/LO1: R8.1, U2.5 (LO)
/ESC2/LO2: R13.1, U3.5 (LO)
/ESC2/LO3: R18.1, U4.5 (LO)
/ESC2/gate_H1: Q1.3 (G), R4.2
/ESC2/gate_H2: Q3.3 (G), R9.2
/ESC2/gate_H3: Q5.3 (G), R17.2
/ESC2/gate_L1: Q2.3 (G), R8.2
/ESC2/gate_L2: Q4.3 (G), R13.2
/ESC2/gate_L3: Q6.3 (G), R18.2
/ESC2/star2: R14.1, R15.1, R16.1, U1.6 (-), U1.9 (-), U1.13 (-)
/RP2040/GPIO0: U7.2 (GPIO0), U9.2 (HI)
/RP2040/GPIO1: U7.3 (GPIO1), U9.3 (LI)
/RP2040/GPIO2: U7.4 (GPIO2), U10.2 (HI)
/RP2040/GPIO3: U7.5 (GPIO3), U10.3 (LI)
/RP2040/GPIO4: U7.6 (GPIO4), U11.2 (HI)
/RP2040/GPIO5: U7.7 (GPIO5), U11.3 (LI)
/RP2040/GPIO6: U7.8 (GPIO6), U8.14
/RP2040/GPIO7: U7.9 (GPIO7), U8.8
/RP2040/GPIO8: U7.11 (GPIO8), U8.7
/RP2040/GPIO10: U2.2 (HI), U7.13 (GPIO10)
/RP2040/GPIO11: U2.3 (LI), U7.14 (GPIO11)
/RP2040/GPIO12: U3.2 (HI), U7.15 (GPIO12)
/RP2040/GPIO13: U3.3 (LI), U7.16 (GPIO13)
/RP2040/GPIO14: U4.2 (HI), U7.17 (GPIO14)
/RP2040/GPIO15: U4.3 (LI), U7.18 (GPIO15)
/RP2040/GPIO16: U1.14, U7.27 (GPIO16)
/RP2040/GPIO17: U1.8, U7.28 (GPIO17)
/RP2040/GPIO18: U1.7, U7.29 (GPIO18)
/RP2040/GPIO25: R36.2, U7.37 (GPIO25)
/RP2040/GPIO25-led: D4.2 (A), R36.1
/RP2040/GPIO29_ADC3: U1.1, U7.41 (GPIO29_ADC3)
/RP2040/QSPI_SCLK: U6.6 (CLK), U7.52 (QSPI_SCLK)
/RP2040/QSPI_SD0: U6.5 (DI(IO0)), U7.53 (QSPI_SD0)
/RP2040/QSPI_SD1: U6.2 (DO(IO1)), U7.55 (QSPI_SD1)
/RP2040/QSPI_SD2: U6.3 (IO2), U7.54 (QSPI_SD2)
/RP2040/QSPI_SD3: U6.7 (IO3), U7.51 (QSPI_SD3)
/RP2040/QSPI_SS: R32.2, R34.1, U6.1 (~CS), U7.56 (QSPI_SS)
/RP2040/RUN: C22.1, R35.1, SW1.2 (B), U7.26 (RUN)
/RP2040/USB+: R31.1, U7.47 (USB_DP)
/RP2040/USB-: R33.1, U7.46 (USB_DM)
/RP2040/V_ADC: C19.1, R30.2, U5.1 (K), U7.43 (ADC_AVDD)
/RP2040/XIN: C15.2, U7.20 (XIN), Y1.1
/RP2040/XOUT: R6.1, U7.21 (XOUT)
/RP2040/XOUT-raw: C16.2, R6.2, Y1.2
/RP2040/~USB_BOOT: J7.1, R34.2
ESC2_VCC: Q1.1 (D), Q3.1 (D), Q5.1 (D), Q7.1 (D), Q9.1 (D), Q11.1 (D), R3.2, R21.2
GND: C1.1, C3.1, C5.1, C8.2, C9.2, C10.2, C11.2, C12.2, C13.2, C14.2, C15.1, C16.1, C17.2, C18.2, C19.2, C20.2, C21.2, C22.2, C23.1, C26.1, C28.1, D4.1 (K), D5.1 (K), J7.2, Q2.2 (S), Q4.2 (S), Q6.2 (S), Q8.2 (S), Q10.2 (S), Q12.2 (S), SW1.1 (A), U1.11 (V-), U2.4 (VSS), U3.4 (VSS), U4.4 (VSS), U5.2 (A), U6.4 (GND), U7.19 (TESTEN), U7.57 (GND), U8.11 (V-), U9.4 (VSS), U10.4 (VSS), U11.4 (VSS)
unnamed: D5.2 (A), R37.1
unnamed: R10.1, R14.2, U1.12 (+)
unnamed: R11.1, R15.2, U1.10 (+)
unnamed: R12.1, R16.2, U1.5 (+)
unnamed: R27.1, R39.2, U8.12 (+)
unnamed: R28.1, R40.2, U8.10 (+)
unnamed: R29.1, R41.2, U8.5 (+)
VCC: R3.1, R21.1
